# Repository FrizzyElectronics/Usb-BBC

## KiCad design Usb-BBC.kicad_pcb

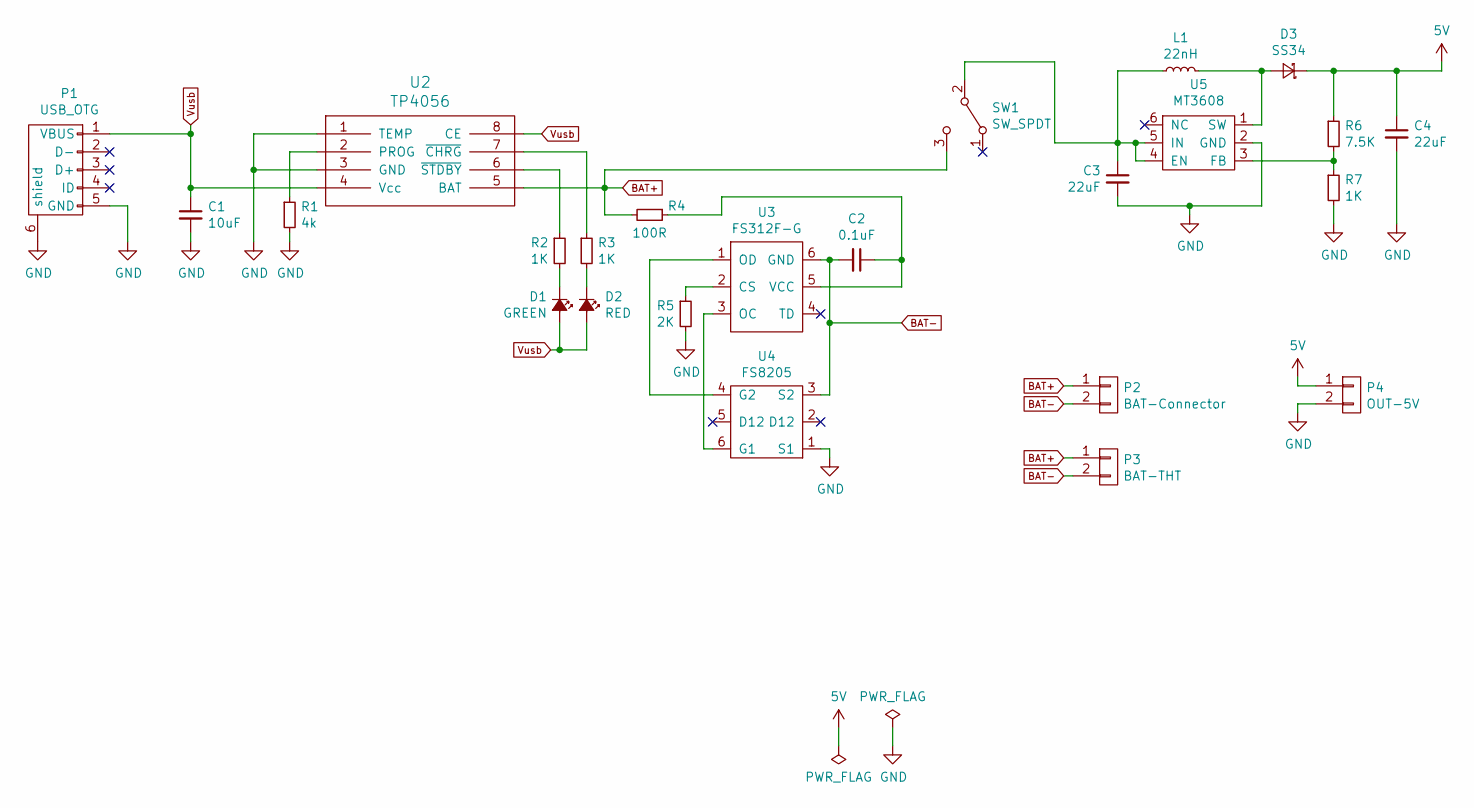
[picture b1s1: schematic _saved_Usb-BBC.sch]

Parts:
C1: 10uF; C_0603
C2: 0.1uF; C_0603
C3, C4: 22uF; C_1812
D1: GREEN; LED_0603_HandSoldering
D2: RED; LED_0603_HandSoldering
D3: SS34; D_SMA
L1: 22nH; L_7.3x7.3_H4.5
P1: USB_OTG; USB_Micro-B_Molex-105017-0001
P2: BAT-Connector; JST_PH_S2B-PH-SM4-TB_02x2.00mm_Angled
P3: BAT-THT; Pin_Header_Straight_1x02_Pitch2.54mm
P4: OUT-5V; Pin_Header_Straight_1x02_Pitch2.54mm
R1: 4k; R_0603
R2, R3, R7: 1K; R_0603
R4: 100R; R_0603
R5: 2K; R_0603
R6: 7.5K; R_0603
SW1: SW_SPDT; SWITCH_SPST_SMD_A
U2: TP4056; HTSOP-8-1EP_3.9x4.9mm_Pitch1.27mm_ThermalVias
U3: FS312F-G; SOT-23-6
U4: FS8205; SOT-23-6
U5: MT3608; SOT-23-6

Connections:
5V: C4.1, D3.1 (K), P4.1, R6.1; also elsewhere on the board
BAT+: P2.1, P3.1, R4.2, SW1.3 (C), U2.5 (BAT)
BAT-: C2.2, P2.2, P3.2, U3.6 (GND), U4.3 (S2)
GND: C1.2, C3.2, C4.2, P1.5 (GND), P1.6 (shield), P4.2, R1.2, R5.2, R7.2, U2.1 (TEMP), U2.3 (GND), U4.1 (S1), U5.2 (GND); also elsewhere on the board
unnamed: C2.1, R4.1, U3.5 (VCC)
unnamed: C3.1, L1.1, SW1.2 (B), U5.4 (EN), U5.5 (IN)
unnamed: D1.1 (K), R2.2
unnamed: D2.1 (K), R3.2
unnamed: D3.2 (A), L1.2, U5.1 (SW)
unnamed: R1.1, U2.2 (PROG)
unnamed: R2.1, U2.6 (~STDBY)
unnamed: R3.1, U2.7 (~CHRG)
unnamed: R5.1, U3.2 (CS)
unnamed: R6.2, R7.1, U5.3 (FB)
unnamed: U3.1 (OD), U4.4 (G2)
unnamed: U3.3 (OC), U4.6 (G1)
Vusb: C1.1, D1.2 (A), D2.2 (A), P1.1 (VBUS), U2.4 (Vcc), U2.8 (CE)

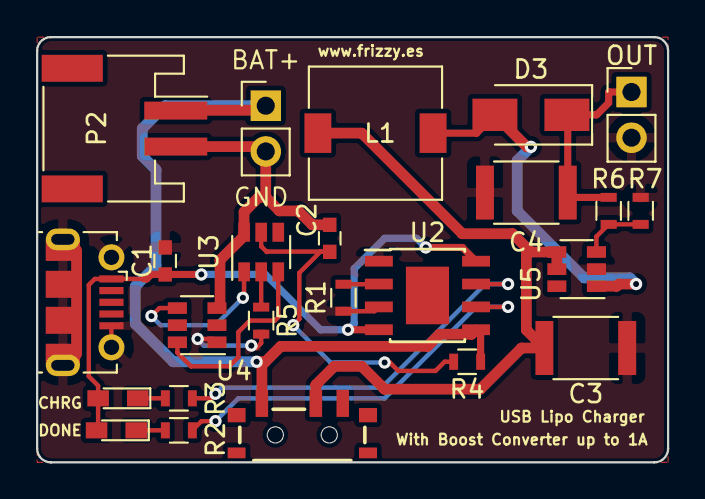
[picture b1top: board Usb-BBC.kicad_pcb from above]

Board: 2 copper layers, 35.1 x 23.6 mm, 24 parts (0 on the bottom side), 17 nets.

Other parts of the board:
OUT: OUT-5V; Pin_Header_Straight_1x02_Pitch2.54mm

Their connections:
5V: OUT.1; also elsewhere on the board
GND: OUT.2; also elsewhere on the board

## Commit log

2018-12-17 CVPCB terminado y placa enrutada
2018-12-17 Mandada a fabrica
2019-02-27 Serigrafía arreglada.
